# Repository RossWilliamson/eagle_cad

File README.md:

eagle_cad
=========

Eagle Projects

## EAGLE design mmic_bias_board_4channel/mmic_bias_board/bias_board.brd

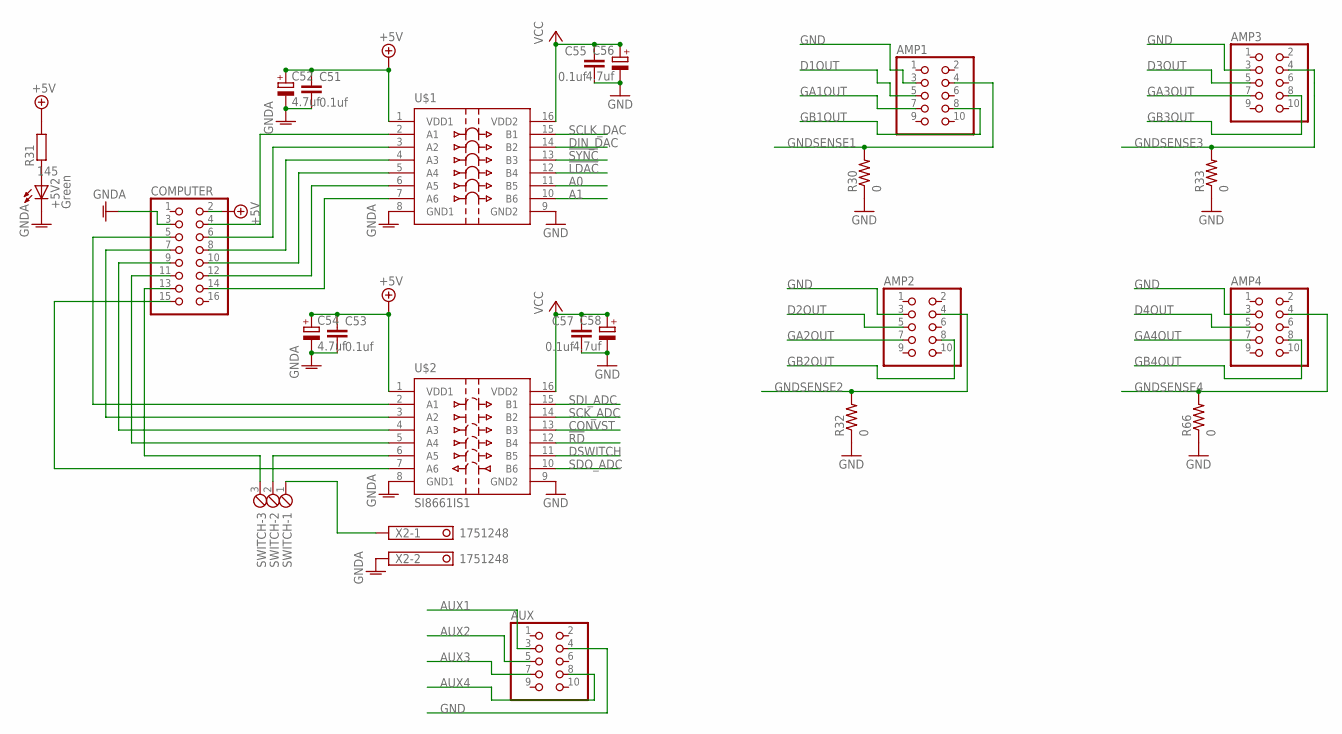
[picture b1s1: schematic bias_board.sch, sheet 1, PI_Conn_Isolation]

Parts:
+5V2: Green; 1206; MPN 01-901.5
AMP1, AMP2, AMP3, AMP4: PINHD-2X5; 2X05
AUX: PINHD-2X5; 2X05
C51, C53, C55, C57: 0.1uf; C1206; PARTNO C1206C104K3RACTU
C52, C54, C56, C58: 4.7uf; A/3216-18W; PARTNO T491A475M025AT
COMPUTER: PINHD-2X8; 2X08
R30, R32, R33, R66: 0; M1206
R31: 145; R1206; MPN MC0.125W12061%147R
SWITCH: MPT3; 3POL254
U$1: SI8660IS1; SO16
U$2: SI8661IS1; SO16
X2: 1751248

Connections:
!LDAC: U$1.12 (B4); also elsewhere on the board
!RD: U$2.12 (B4); also elsewhere on the board
!SYNC: U$1.13 (B3); also elsewhere on the board
+5V: C51.1, C52.+, C53.1, C54.+, COMPUTER.2, R31.2, U$1.1 (VDD1), U$2.1 (VDD1)
A0: U$1.11 (B5); also elsewhere on the board
A1: U$1.10 (B6); also elsewhere on the board
AUX1: AUX.3; also elsewhere on the board
AUX2: AUX.5; also elsewhere on the board
AUX3: AUX.7; also elsewhere on the board
AUX4: AUX.8; also elsewhere on the board
CONVST: U$2.13 (B3); also elsewhere on the board
D1OUT: AMP1.5; also elsewhere on the board
D2OUT: AMP2.5; also elsewhere on the board
D3OUT: AMP3.5; also elsewhere on the board
D4OUT: AMP4.5; also elsewhere on the board
DIN_DAC: U$1.14 (B2); also elsewhere on the board
DSWITCH: U$2.11 (B5); also elsewhere on the board
GA1OUT: AMP1.7; also elsewhere on the board
GA2OUT: AMP2.7; also elsewhere on the board
GA3OUT: AMP3.7; also elsewhere on the board
GA4OUT: AMP4.7; also elsewhere on the board
GB1OUT: AMP1.8; also elsewhere on the board
GB2OUT: AMP2.8; also elsewhere on the board
GB3OUT: AMP3.8; also elsewhere on the board
GB4OUT: AMP4.8; also elsewhere on the board
GND: AMP1.3, AMP2.3, AMP3.3, AMP4.3, AUX.4, C55.2, C56.-, C57.2, C58.-, R30.1, R32.1, R33.1, R66.1, U$1.9 (GND2), U$2.9 (GND2); also elsewhere on the board
GNDA: +5V2.C, C51.2, C52.-, C53.2, C54.-, COMPUTER.3, U$1.8 (GND1), U$2.8 (GND1), X2.2
GNDSENSE1: AMP1.4, R30.2; also elsewhere on the board
GNDSENSE2: AMP2.4, R32.2; also elsewhere on the board
GNDSENSE3: AMP3.4, R33.2; also elsewhere on the board
GNDSENSE4: AMP4.4, R66.2; also elsewhere on the board
unnamed: COMPUTER.10, U$1.5 (A4)
unnamed: COMPUTER.12, U$1.6 (A5)
unnamed: COMPUTER.11, U$2.5 (A4)
unnamed: COMPUTER.4, U$1.2 (A1)
unnamed: COMPUTER.6, U$1.3 (A2)
unnamed: COMPUTER.8, U$1.4 (A3)
unnamed: COMPUTER.5, U$2.2 (A1)
unnamed: COMPUTER.7, U$2.3 (A2)
unnamed: COMPUTER.9, U$2.4 (A3)
unnamed: COMPUTER.13, SWITCH.3
unnamed: COMPUTER.15, U$2.7 (A6)
unnamed: +5V2.A, R31.1
unnamed: SWITCH.2, U$2.6 (A5)
unnamed: SWITCH.1, X2.1
unnamed: COMPUTER.14, U$1.7 (A6)
SCK_ADC: U$2.14 (B2); also elsewhere on the board
SCLK_DAC: U$1.15 (B1); also elsewhere on the board
SDI_ADC: U$2.15 (B1); also elsewhere on the board
SDO_ADC: U$2.10 (B6); also elsewhere on the board
VCC: C55.1, C56.+, C57.1, C58.+, U$1.16 (VDD2), U$2.16 (VDD2); also elsewhere on the board

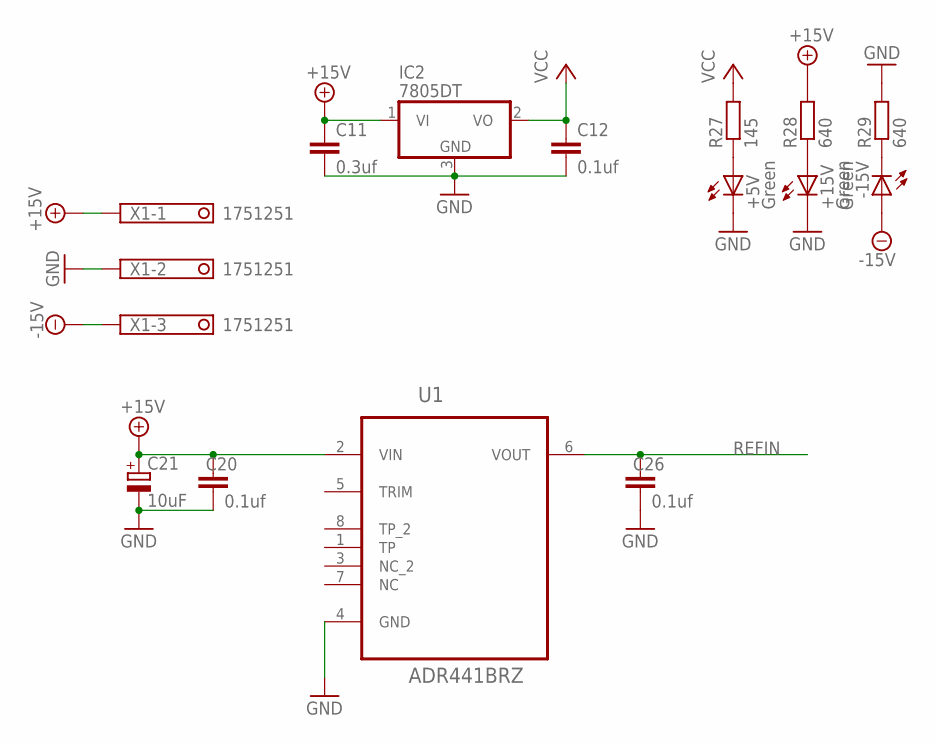
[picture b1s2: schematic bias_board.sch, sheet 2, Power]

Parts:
+5V, +15V: Green; 1206; MPN 01-901.5
-15V: Green; 1206; MPN 01-901.5
C11: 0.3uf; C1206; PARTNO C3216X7R1E334K
C12, C20, C26: 0.1uf; C1206; PARTNO C1206C104K3RACTU
C21: 10uF; A/3216-18W; PARTNO T491A475M025AT
IC2: 7805DT; TO252; PARTNO BA17805FP-E2
R27: 145; R1206; MPN MC0.125W12061%147R
R28, R29: 640; R1206; MPN MC0.125W12061%649R
U1: ADR441BRZ; SOIC127P600X175-8N
X1: 1751251

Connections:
+15V: C11.1, C20.1, C21.+, IC2.1 (VI), R28.2, U1.2 (VIN), X1.1; also elsewhere on the board
-15V: -15V.A, X1.3; also elsewhere on the board
GND: +5V.C, +15V.C, C11.2, C12.2, C20.2, C21.-, C26.2, IC2.3 (GND), R29.2, U1.4 (GND), X1.2; also elsewhere on the board
unnamed: +5V.A, R27.1
unnamed: +15V.A, R28.1
unnamed: -15V.C, R29.1
REFIN: C26.1, U1.6 (VOUT); also elsewhere on the board
VCC: C12.1, IC2.2 (VO), R27.2; also elsewhere on the board

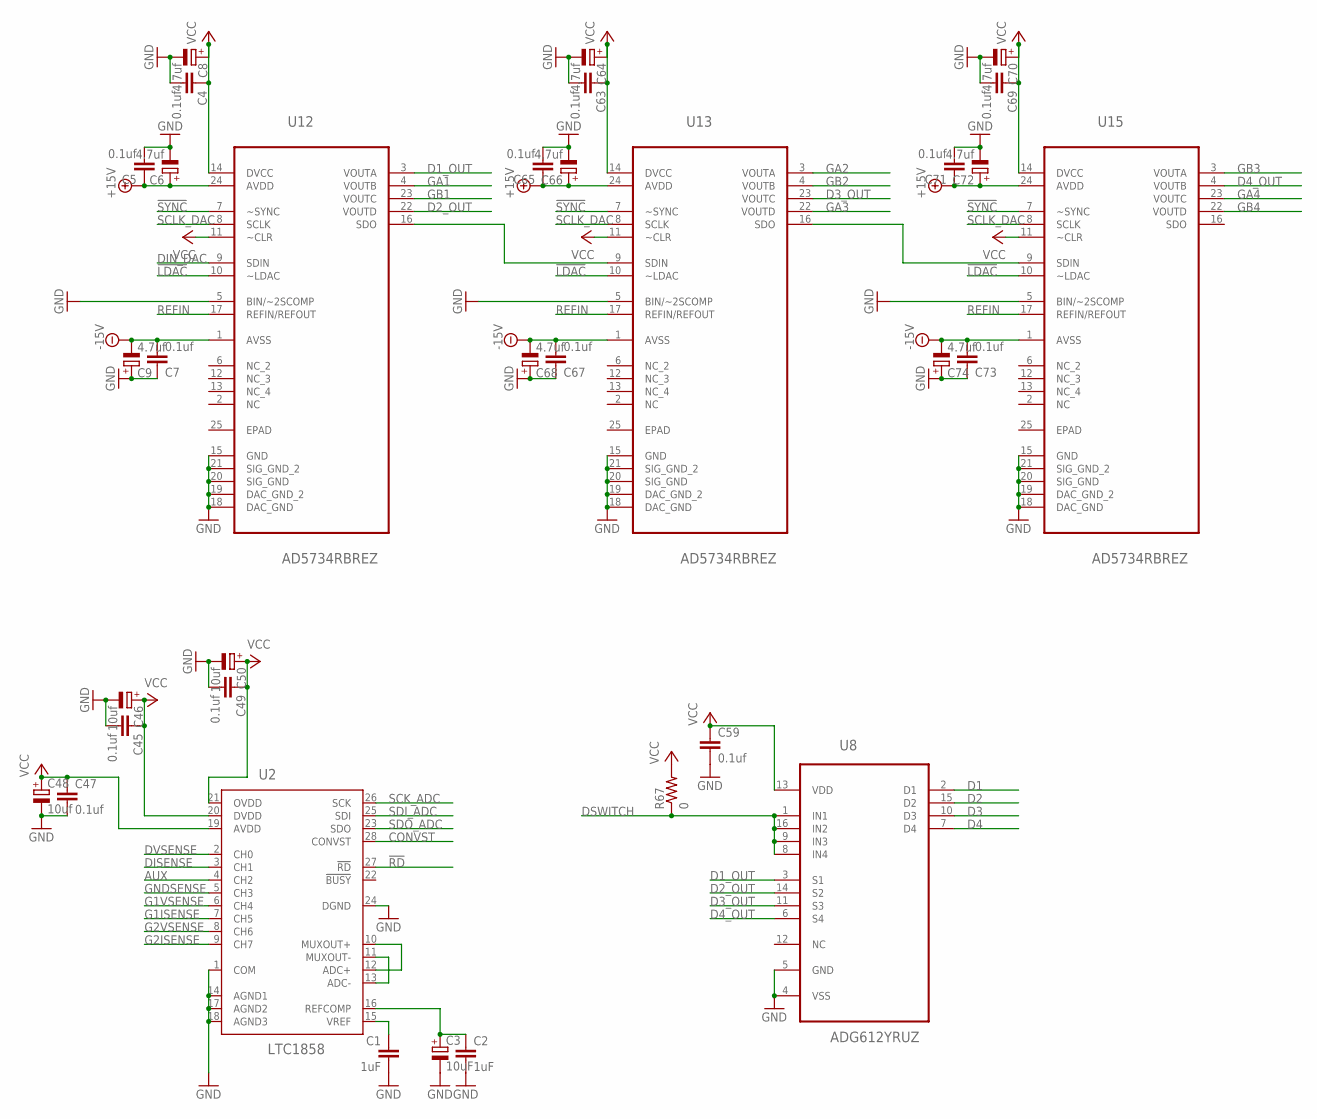
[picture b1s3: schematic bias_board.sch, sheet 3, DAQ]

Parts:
C1, C2: 1uF; C1206; PARTNO C1206C104K3RACTU
C3: 10uF; A/3216-18W; PARTNO T491A475M025AT
C4, C5, C7, C45, C47, C49, C59, C63, C65, C67, C69, C71, C73: 0.1uf; C1206; PARTNO C1206C104K3RACTU
C6, C8, C9, C64, C66, C68, C70, C72, C74: 4.7uf; A/3216-18W; PARTNO T491A475M025AT
C46, C48, C50: 10uf; A/3216-18W; PARTNO T491A475M025AT
R67: 0; M1206
U2: LTC1858; SSOP28
U8: ADG612YRUZ; SOP65P640X120-16N
U12, U13, U15: AD5734RBREZ; SOP65P640X120-25N

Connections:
!LDAC: U12.10 (~LDAC), U13.10 (~LDAC), U15.10 (~LDAC); also elsewhere on the board
!RD: U2.27 (!RD); also elsewhere on the board
!SYNC: U12.7 (~SYNC), U13.7 (~SYNC), U15.7 (~SYNC); also elsewhere on the board
+15V: C5.1, C6.+, C65.1, C66.+, C71.1, C72.+, U12.24 (AVDD), U13.24 (AVDD), U15.24 (AVDD); also elsewhere on the board
-15V: C7.2, C9.-, C67.2, C68.-, C73.2, C74.-, U12.1 (AVSS), U13.1 (AVSS), U15.1 (AVSS); also elsewhere on the board
AUX: U2.4 (CH2); also elsewhere on the board
CONVST: U2.28 (CONVST); also elsewhere on the board
D1: U8.2 (D1); also elsewhere on the board
D1_OUT: U8.3 (S1), U12.3 (VOUTA)
D2: U8.15 (D2); also elsewhere on the board
D2_OUT: U8.14 (S2), U12.22 (VOUTD)
D3: U8.10 (D3); also elsewhere on the board
D3_OUT: U8.11 (S3), U13.23 (VOUTC)
D4: U8.7 (D4); also elsewhere on the board
D4_OUT: U8.6 (S4), U15.4 (VOUTB)
DIN_DAC: U12.9 (SDIN); also elsewhere on the board
DISENSE: U2.3 (CH1); also elsewhere on the board
DSWITCH: R67.1, U8.1 (IN1), U8.8 (IN4), U8.9 (IN3), U8.16 (IN2); also elsewhere on the board
DVSENSE: U2.2 (CH0); also elsewhere on the board
EPAD: U12.25 (EPAD), U13.25 (EPAD), U15.25 (EPAD)
G1ISENSE: U2.7 (CH5); also elsewhere on the board
G1VSENSE: U2.6 (CH4); also elsewhere on the board
G2ISENSE: U2.9 (CH7); also elsewhere on the board
G2VSENSE: U2.8 (CH6); also elsewhere on the board
GA1: U12.4 (VOUTB); also elsewhere on the board
GA2: U13.3 (VOUTA); also elsewhere on the board
GA3: U13.22 (VOUTD); also elsewhere on the board
GA4: U15.23 (VOUTC); also elsewhere on the board
GB1: U12.23 (VOUTC); also elsewhere on the board
GB2: U13.4 (VOUTB); also elsewhere on the board
GB3: U15.3 (VOUTA); also elsewhere on the board
GB4: U15.22 (VOUTD); also elsewhere on the board
GND: C1.2, C2.2, C3.-, C4.2, C5.2, C6.-, C7.1, C8.-, C9.+, C45.2, C46.-, C47.2, C48.-, C49.2, C50.-, C59.2, C63.2, C64.-, C65.2, C66.-, C67.1, C68.+, C69.2, C70.-, C71.2, C72.-, C73.1, C74.+, U2.1 (COM), U2.14 (AGND1), U2.17 (AGND2), U2.18 (AGND3), U2.24 (DGND), U8.4 (VSS), U8.5 (GND), U12.5 (BIN/~2SCOMP), U12.15 (GND), U12.18 (DAC_GND), U12.19 (DAC_GND_2), U12.20 (SIG_GND), U12.21 (SIG_GND_2), U13.5 (BIN/~2SCOMP), U13.15 (GND), U13.18 (DAC_GND), U13.19 (DAC_GND_2), U13.20 (SIG_GND), U13.21 (SIG_GND_2), U15.5 (BIN/~2SCOMP), U15.15 (GND), U15.18 (DAC_GND), U15.19 (DAC_GND_2), U15.20 (SIG_GND), U15.21 (SIG_GND_2); also elsewhere on the board
GNDSENSE: U2.5 (CH3); also elsewhere on the board
unnamed: C1.1, U2.15 (VREF)
unnamed: C2.1, C3.+, U2.16 (REFCOMP)
unnamed: U2.10 (MUXOUT+), U2.12 (ADC+)
unnamed: U2.11 (MUXOUT-), U2.13 (ADC-)
unnamed: U12.16 (SDO), U13.9 (SDIN)
unnamed: U13.16 (SDO), U15.9 (SDIN)
REFIN: U12.17 (REFIN/REFOUT), U13.17 (REFIN/REFOUT), U15.17 (REFIN/REFOUT); also elsewhere on the board
SCK_ADC: U2.26 (SCK); also elsewhere on the board
SCLK_DAC: U12.8 (SCLK), U13.8 (SCLK), U15.8 (SCLK); also elsewhere on the board
SDI_ADC: U2.25 (SDI); also elsewhere on the board
SDO_ADC: U2.23 (SDO); also elsewhere on the board
VCC: C4.1, C8.+, C45.1, C46.+, C47.1, C48.+, C49.1, C50.+, C59.1, C63.1, C64.+, C69.1, C70.+, R67.2, U2.19 (AVDD), U2.20 (DVDD), U2.21 (OVDD), U8.13 (VDD), U12.11 (~CLR), U12.14 (DVCC), U13.11 (~CLR), U13.14 (DVCC), U15.11 (~CLR), U15.14 (DVCC); also elsewhere on the board

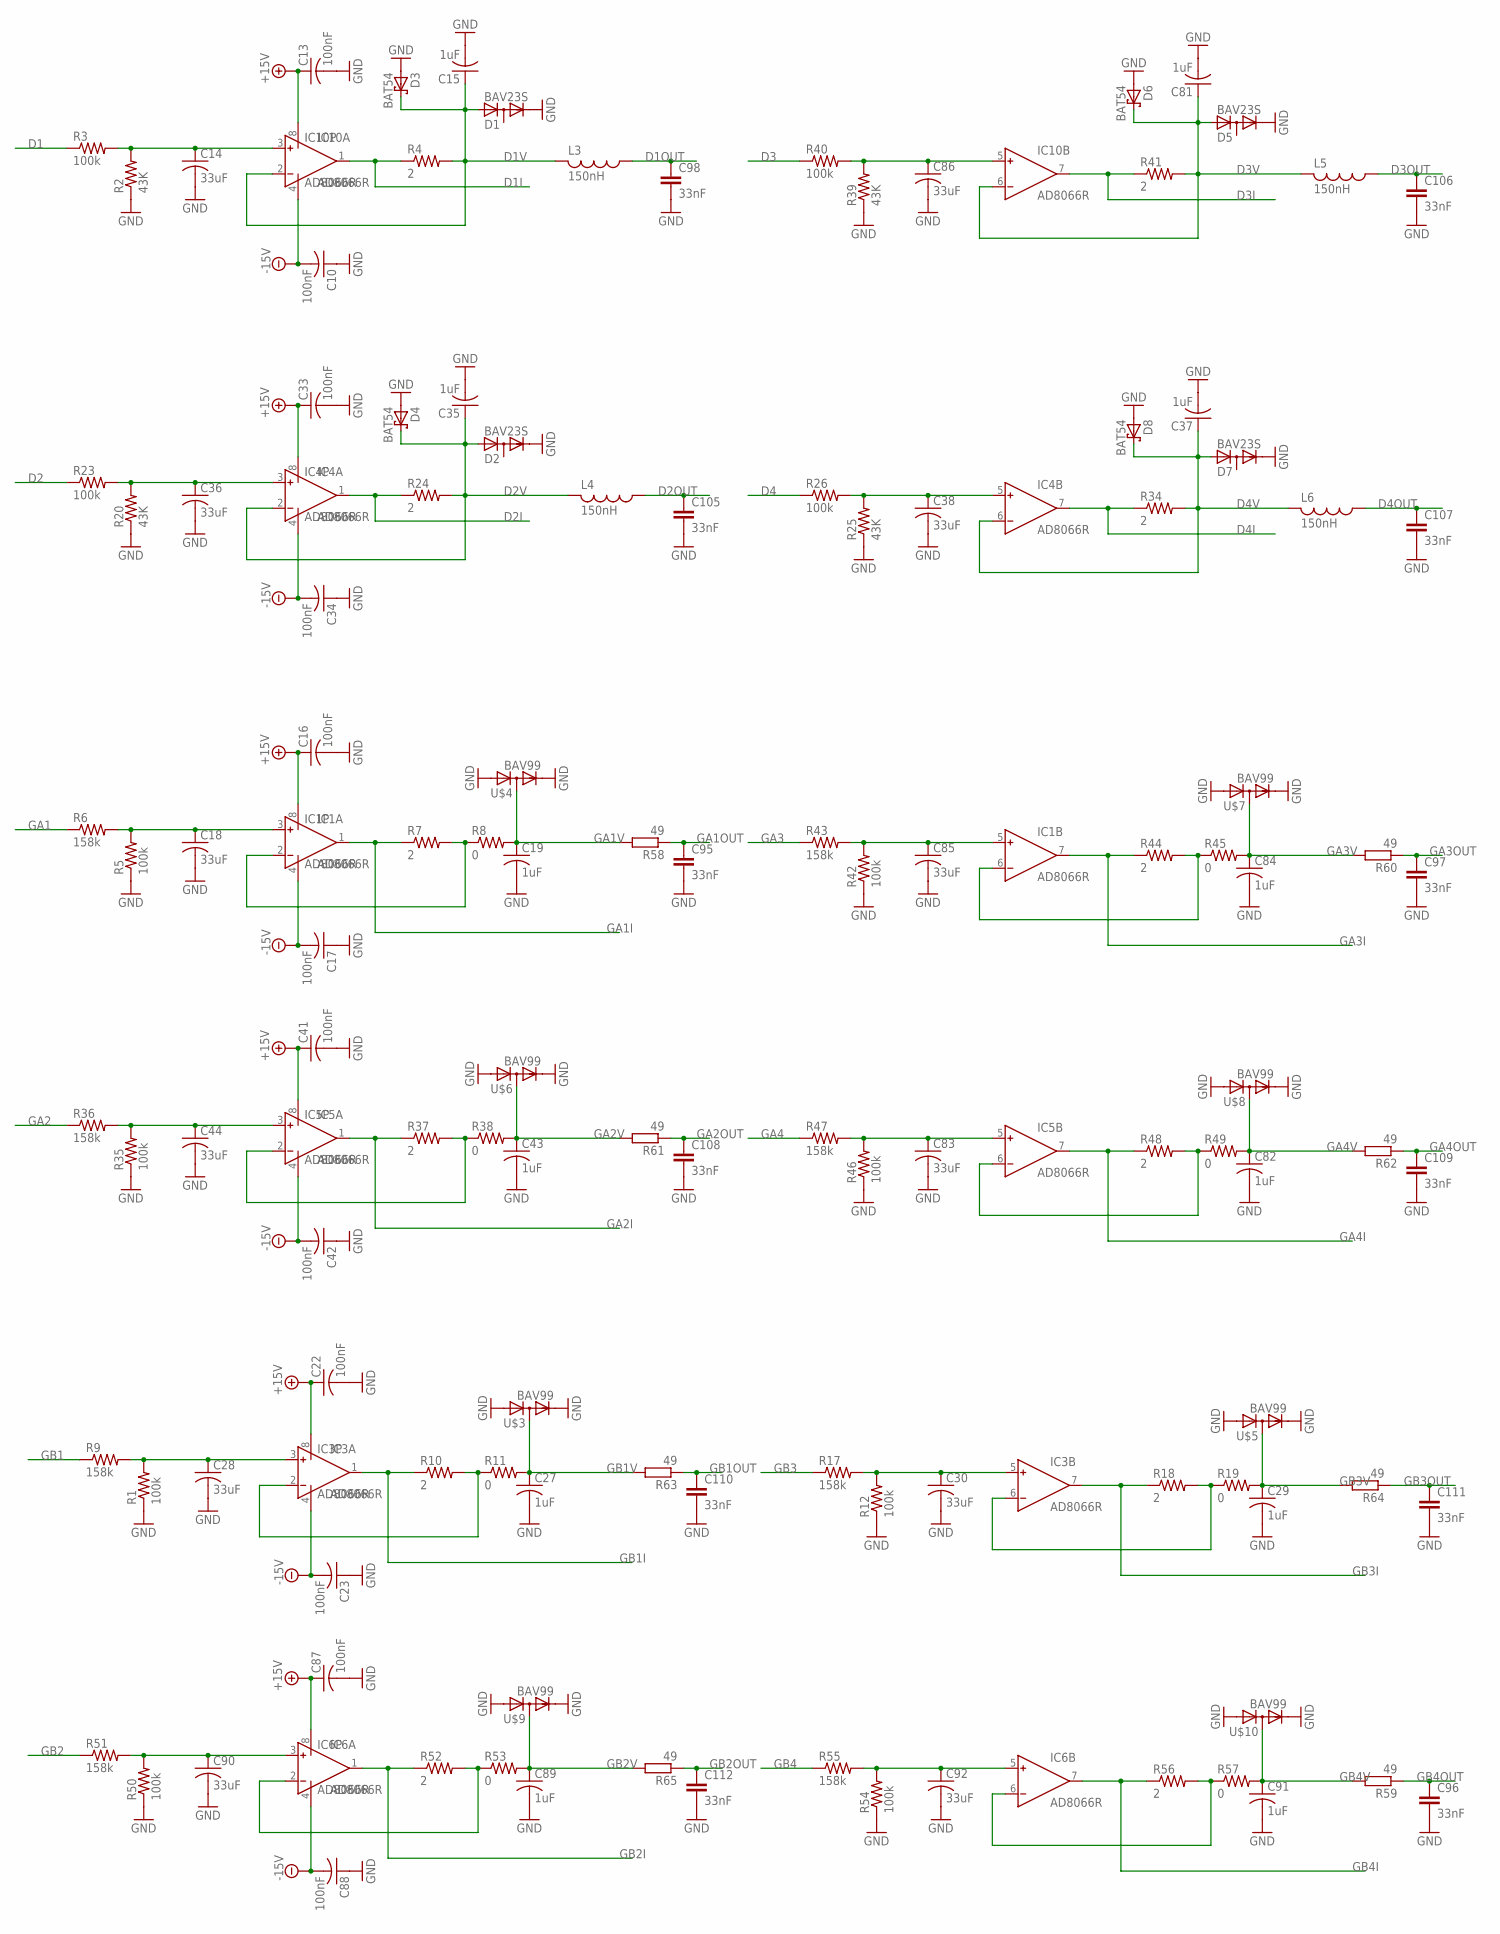
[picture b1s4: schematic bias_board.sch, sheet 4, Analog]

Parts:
C10, C13, C16, C17, C22, C23, C33, C34, C41, C42, C87, C88: 100nF; C1206K
C14, C18, C28, C30, C36, C38, C44, C83, C85, C86, C90, C92: 33uF; C1206K
C15, C19, C27, C29, C35, C37, C43, C81, C82, C84, C89, C91: 1uF; C1206K
C95, C96, C97, C98, C105, C106, C107, C108, C109, C110, C111, C112: 33nF; C1206; PARTNO C1206C104K3RACTU
D1, D2, D5, D7: BAV23S; SOT23
D3, D4, D6, D8: BAT54; SOT23
IC1, IC3, IC4, IC5, IC6, IC10: AD8066R; SO8
L3, L4, L5, L6: 150nH; L3225M
R1, R3, R5, R12, R23, R26, R35, R40, R42, R46, R50, R54: 100k; M1206
R2, R20, R25, R39: 43K; M1206
R4, R7, R10, R18, R24, R34, R37, R41, R44, R48, R52, R56: 2; M1206
R6, R9, R17, R36, R43, R47, R51, R55: 158k; M1206
R8, R11, R19, R38, R45, R49, R53, R57: 0; M1206
R58, R59, R60, R61, R62, R63, R64, R65: 49; R1206; MPN MC0.125W12061%147R
U$3, U$4, U$5, U$6, U$7, U$8, U$9, U$10: BAV99; SOT23

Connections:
+15V: C13.1, C16.1, C22.1, C33.1, C41.1, C87.1, IC1.8 (V+), IC3.8 (V+), IC4.8 (V+), IC5.8 (V+), IC6.8 (V+), IC10.8 (V+); also elsewhere on the board
-15V: C10.2, C17.2, C23.2, C34.2, C42.2, C88.2, IC1.4 (V-), IC3.4 (V-), IC4.4 (V-), IC5.4 (V-), IC6.4 (V-), IC10.4 (V-); also elsewhere on the board
D1: R3.1; also elsewhere on the board
D1I: IC10.1 (OUT), R4.1; also elsewhere on the board
D1OUT: C98.1, L3.1; also elsewhere on the board
D1V: C15.1, D1.1 (A), D3.3 (C), IC10.2 (IN-), L3.2, R4.2; also elsewhere on the board
D2: R23.1; also elsewhere on the board
D2I: IC4.1 (OUT), R24.1; also elsewhere on the board
D2OUT: C105.1, L4.1; also elsewhere on the board
D2V: C35.1, D2.1 (A), D4.3 (C), IC4.2 (IN-), L4.2, R24.2; also elsewhere on the board
D3: R40.1; also elsewhere on the board
D3I: IC10.7 (OUT), R41.1; also elsewhere on the board
D3OUT: C106.1, L5.1; also elsewhere on the board
D3V: C81.1, D5.1 (A), D6.3 (C), IC10.6 (IN-), L5.2, R41.2; also elsewhere on the board
D4: R26.1; also elsewhere on the board
D4I: IC4.7 (OUT), R34.1; also elsewhere on the board
D4OUT: C107.1, L6.1; also elsewhere on the board
D4V: C37.1, D7.1 (A), D8.3 (C), IC4.6 (IN-), L6.2, R34.2; also elsewhere on the board
GA1: R6.1; also elsewhere on the board
GA1I: IC1.1 (OUT), R7.1; also elsewhere on the board
GA1OUT: C95.1, R58.1; also elsewhere on the board
GA1V: C19.1, R8.2, R58.2, U$4.3 (AC); also elsewhere on the board
GA2: R36.1; also elsewhere on the board
GA2I: IC5.1 (OUT), R37.1; also elsewhere on the board
GA2OUT: C108.1, R61.1; also elsewhere on the board
GA2V: C43.1, R38.2, R61.2, U$6.3 (AC); also elsewhere on the board
GA3: R43.1; also elsewhere on the board
GA3I: IC1.7 (OUT), R44.1; also elsewhere on the board
GA3OUT: C97.1, R60.1; also elsewhere on the board
GA3V: C84.1, R45.2, R60.2, U$7.3 (AC); also elsewhere on the board
GA4: R47.1; also elsewhere on the board
GA4I: IC5.7 (OUT), R48.1; also elsewhere on the board
GA4OUT: C109.1, R62.1; also elsewhere on the board
GA4V: C82.1, R49.2, R62.2, U$8.3 (AC); also elsewhere on the board
GB1: R9.1; also elsewhere on the board
GB1I: IC3.1 (OUT), R10.1; also elsewhere on the board
GB1OUT: C110.1, R63.1; also elsewhere on the board
GB1V: C27.1, R11.2, R63.2, U$3.3 (AC); also elsewhere on the board
GB2: R51.1; also elsewhere on the board
GB2I: IC6.1 (OUT), R52.1; also elsewhere on the board
GB2OUT: C112.1, R65.1; also elsewhere on the board
GB2V: C89.1, R53.2, R65.2, U$9.3 (AC); also elsewhere on the board
GB3: R17.1; also elsewhere on the board
GB3I: IC3.7 (OUT), R18.1; also elsewhere on the board
GB3OUT: C111.1, R64.1; also elsewhere on the board
GB3V: C29.1, R19.2, R64.2, U$5.3 (AC); also elsewhere on the board
GB4: R55.1; also elsewhere on the board
GB4I: IC6.7 (OUT), R56.1; also elsewhere on the board
GB4OUT: C96.1, R59.1; also elsewhere on the board
GB4V: C91.1, R57.2, R59.2, U$10.3 (AC); also elsewhere on the board
GND: C10.1, C13.2, C14.2, C15.2, C16.2, C17.1, C18.2, C19.2, C22.2, C23.1, C27.2, C28.2, C29.2, C30.2, C33.2, C34.1, C35.2, C36.2, C37.2, C38.2, C41.2, C42.1, C43.2, C44.2, C81.2, C82.2, C83.2, C84.2, C85.2, C86.2, C87.2, C88.1, C89.2, C90.2, C91.2, C92.2, C95.2, C96.2, C97.2, C98.2, C105.2, C106.2, C107.2, C108.2, C109.2, C110.2, C111.2, C112.2, D1.2 (C), D2.2 (C), D3.1 (A), D4.1 (A), D5.2 (C), D6.1 (A), D7.2 (C), D8.1 (A), R1.1, R2.1, R5.1, R12.1, R20.1, R25.1, R35.1, R39.1, R42.1, R46.1, R50.1, R54.1, U$3.1 (A), U$3.2 (C), U$4.1 (A), U$4.2 (C), U$5.1 (A), U$5.2 (C), U$6.1 (A), U$6.2 (C), U$7.1 (A), U$7.2 (C), U$8.1 (A), U$8.2 (C), U$9.1 (A), U$9.2 (C), U$10.1 (A), U$10.2 (C); also elsewhere on the board
unnamed: C14.1, IC10.3 (IN+), R2.2, R3.2
unnamed: C28.1, IC3.3 (IN+), R1.2, R9.2
unnamed: C18.1, IC1.3 (IN+), R5.2, R6.2
unnamed: IC3.2 (IN-), R10.2, R11.1
unnamed: C30.1, IC3.5 (IN+), R12.2, R17.2
unnamed: IC1.2 (IN-), R7.2, R8.1
unnamed: IC3.6 (IN-), R18.2, R19.1
unnamed: C36.1, IC4.3 (IN+), R20.2, R23.2
unnamed: C38.1, IC4.5 (IN+), R25.2, R26.2
unnamed: C44.1, IC5.3 (IN+), R35.2, R36.2
unnamed: C86.1, IC10.5 (IN+), R39.2, R40.2
unnamed: C85.1, IC1.5 (IN+), R42.2, R43.2
unnamed: IC1.6 (IN-), R44.2, R45.1
unnamed: IC5.2 (IN-), R37.2, R38.1
unnamed: C83.1, IC5.5 (IN+), R46.2, R47.2
unnamed: IC5.6 (IN-), R48.2, R49.1
unnamed: C90.1, IC6.3 (IN+), R50.2, R51.2
unnamed: IC6.2 (IN-), R52.2, R53.1
unnamed: C92.1, IC6.5 (IN+), R54.2, R55.2
unnamed: IC6.6 (IN-), R56.2, R57.1

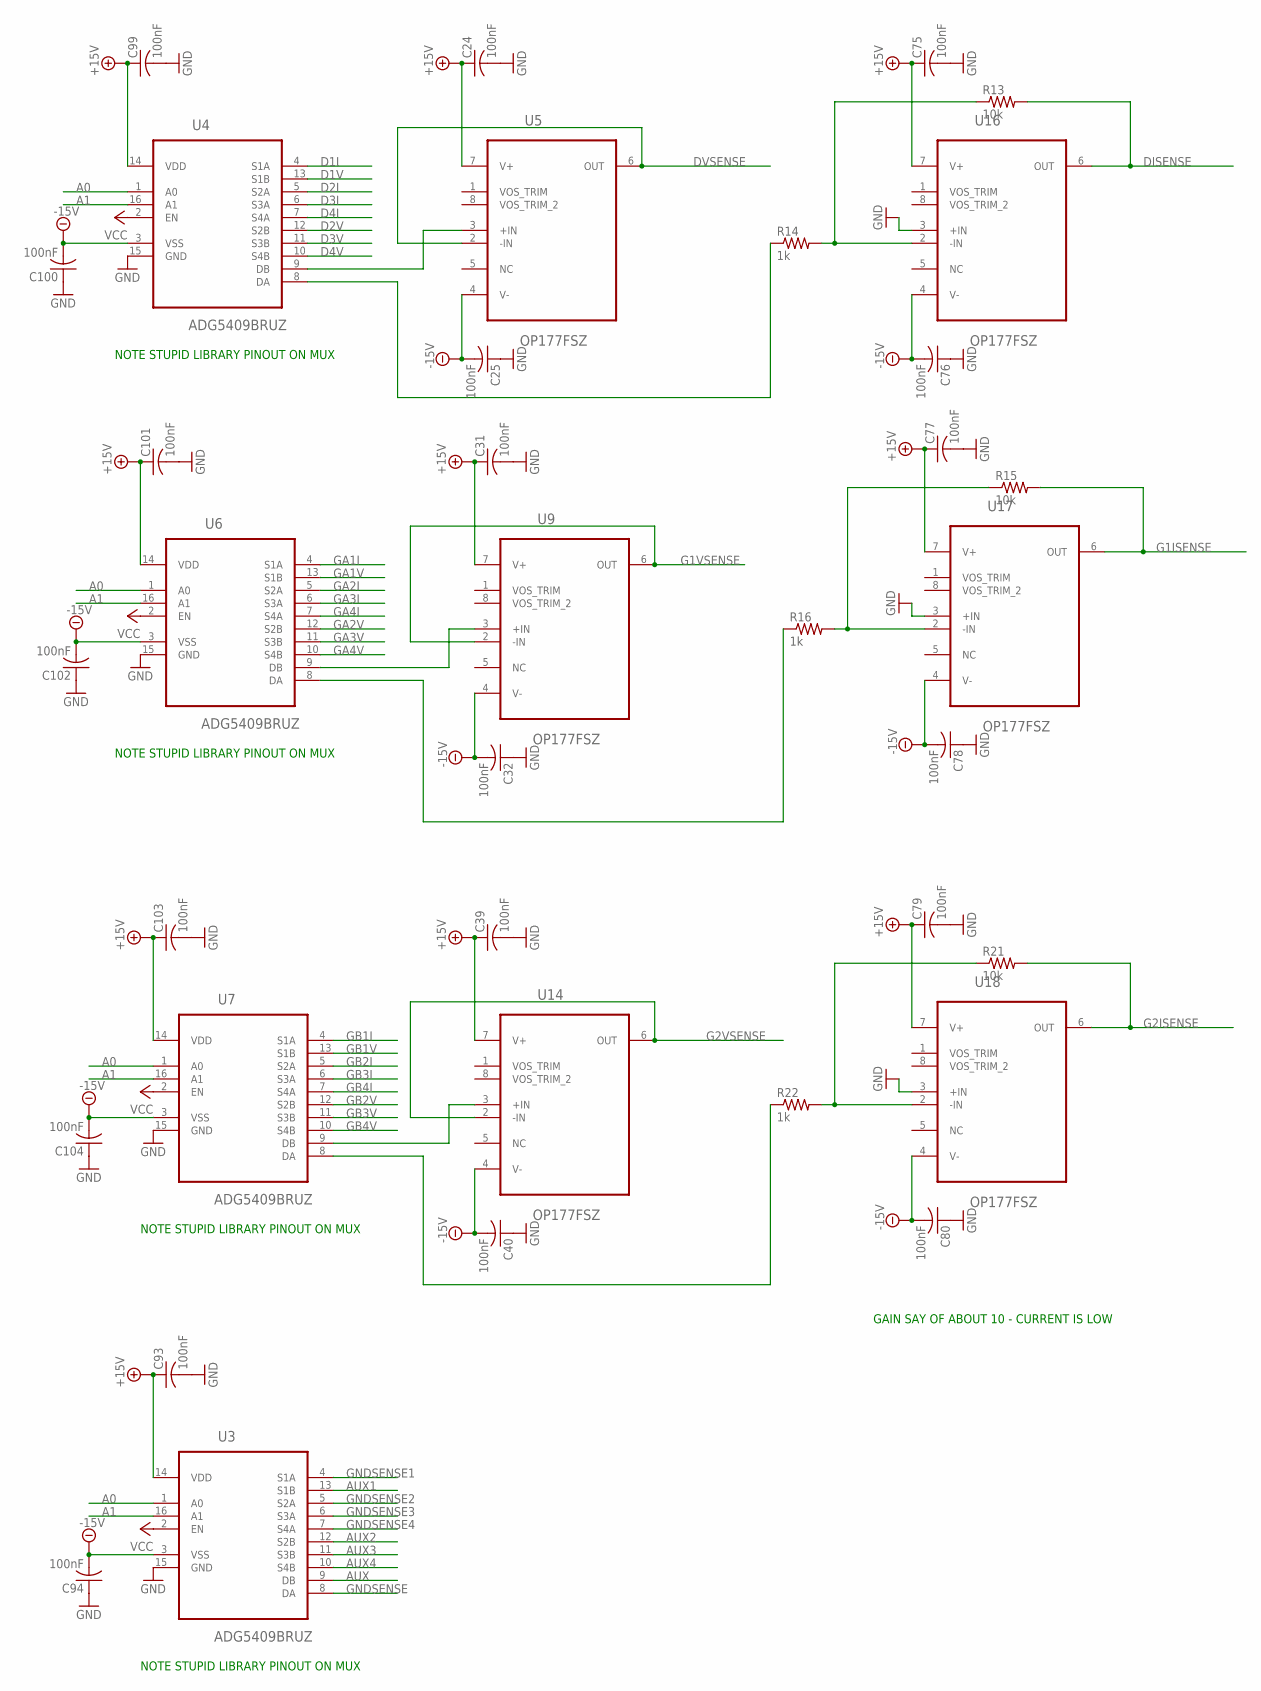
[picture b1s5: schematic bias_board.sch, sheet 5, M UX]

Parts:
C24, C25, C31, C32, C39, C40, C75, C76, C77, C78, C79, C80, C93, C94, C99, C100, C101, C102, C103, C104: 100nF; C1206K
R13, R15, R21: 10k; M1206
R14, R16, R22: 1k; M1206
U3, U4, U6, U7: ADG5409BRUZ; SOP65P640X120-16N
U5, U9, U14, U16, U17, U18: OP177FSZ; SOIC127P600X175-8N

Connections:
+15V: C24.1, C31.1, C39.1, C75.1, C77.1, C79.1, C93.1, C99.1, C101.1, C103.1, U3.14 (VDD), U4.14 (VDD), U5.7 (V+), U6.14 (VDD), U7.14 (VDD), U9.7 (V+), U14.7 (V+), U16.7 (V+), U17.7 (V+), U18.7 (V+); also elsewhere on the board
-15V: C25.2, C32.2, C40.2, C76.2, C78.2, C80.2, C94.2, C100.2, C102.2, C104.2, U3.3 (VSS), U4.3 (VSS), U5.4 (V-), U6.3 (VSS), U7.3 (VSS), U9.4 (V-), U14.4 (V-), U16.4 (V-), U17.4 (V-), U18.4 (V-); also elsewhere on the board
A0: U3.1 (A0), U4.1 (A0), U6.1 (A0), U7.1 (A0); also elsewhere on the board
A1: U3.16 (A1), U4.16 (A1), U6.16 (A1), U7.16 (A1); also elsewhere on the board
AUX: U3.9 (DB); also elsewhere on the board
AUX1: U3.13 (S1B); also elsewhere on the board
AUX2: U3.12 (S2B); also elsewhere on the board
AUX3: U3.11 (S3B); also elsewhere on the board
AUX4: U3.10 (S4B); also elsewhere on the board
D1I: U4.4 (S1A); also elsewhere on the board
D1V: U4.13 (S1B); also elsewhere on the board
D2I: U4.5 (S2A); also elsewhere on the board
D2V: U4.12 (S2B); also elsewhere on the board
D3I: U4.6 (S3A); also elsewhere on the board
D3V: U4.11 (S3B); also elsewhere on the board
D4I: U4.7 (S4A); also elsewhere on the board
D4V: U4.10 (S4B); also elsewhere on the board
DISENSE: R13.2, U16.6 (OUT); also elsewhere on the board
DVSENSE: U5.2 (-IN), U5.6 (OUT); also elsewhere on the board
G1ISENSE: R15.2, U17.6 (OUT); also elsewhere on the board
G1V1: U6.9 (DB), U9.3 (+IN)
G1VSENSE: U9.2 (-IN), U9.6 (OUT); also elsewhere on the board
G2ISENSE: R21.2, U18.6 (OUT); also elsewhere on the board
G2VSENSE: U14.2 (-IN), U14.6 (OUT); also elsewhere on the board
GA1I: U6.4 (S1A); also elsewhere on the board
GA1V: U6.13 (S1B); also elsewhere on the board
GA2I: U6.5 (S2A); also elsewhere on the board
GA2V: U6.12 (S2B); also elsewhere on the board
GA3I: U6.6 (S3A); also elsewhere on the board
GA3V: U6.11 (S3B); also elsewhere on the board
GA4I: U6.7 (S4A); also elsewhere on the board
GA4V: U6.10 (S4B); also elsewhere on the board
GB1I: U7.4 (S1A); also elsewhere on the board
GB1V: U7.13 (S1B); also elsewhere on the board
GB2I: U7.5 (S2A); also elsewhere on the board
GB2V: U7.12 (S2B); also elsewhere on the board
GB3I: U7.6 (S3A); also elsewhere on the board
GB3V: U7.11 (S3B); also elsewhere on the board
GB4I: U7.7 (S4A); also elsewhere on the board
GB4V: U7.10 (S4B); also elsewhere on the board
GND: C24.2, C25.1, C31.2, C32.1, C39.2, C40.1, C75.2, C76.1, C77.2, C78.1, C79.2, C80.1, C93.2, C94.1, C99.2, C100.1, C101.2, C102.1, C103.2, C104.1, U3.15 (GND), U4.15 (GND), U6.15 (GND), U7.15 (GND), U16.3 (+IN), U17.3 (+IN), U18.3 (+IN); also elsewhere on the board
GNDSENSE: U3.8 (DA); also elsewhere on the board
GNDSENSE1: U3.4 (S1A); also elsewhere on the board
GNDSENSE2: U3.5 (S2A); also elsewhere on the board
GNDSENSE3: U3.6 (S3A); also elsewhere on the board
GNDSENSE4: U3.7 (S4A); also elsewhere on the board
unnamed: R13.1, R14.2, U16.2 (-IN)
unnamed: R15.1, R16.2, U17.2 (-IN)
unnamed: R21.1, R22.2, U18.2 (-IN)
unnamed: U4.9 (DB), U5.3 (+IN)
unnamed: R14.1, U4.8 (DA)
unnamed: R16.1, U6.8 (DA)
unnamed: U7.9 (DB), U14.3 (+IN)
unnamed: R22.1, U7.8 (DA)
VCC: U3.2 (EN), U4.2 (EN), U6.2 (EN), U7.2 (EN); also elsewhere on the board

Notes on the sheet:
GAIN SAY OF ABOUT 10 - CURRENT IS LOW
NOTE STUPID LIBRARY PINOUT ON MUX

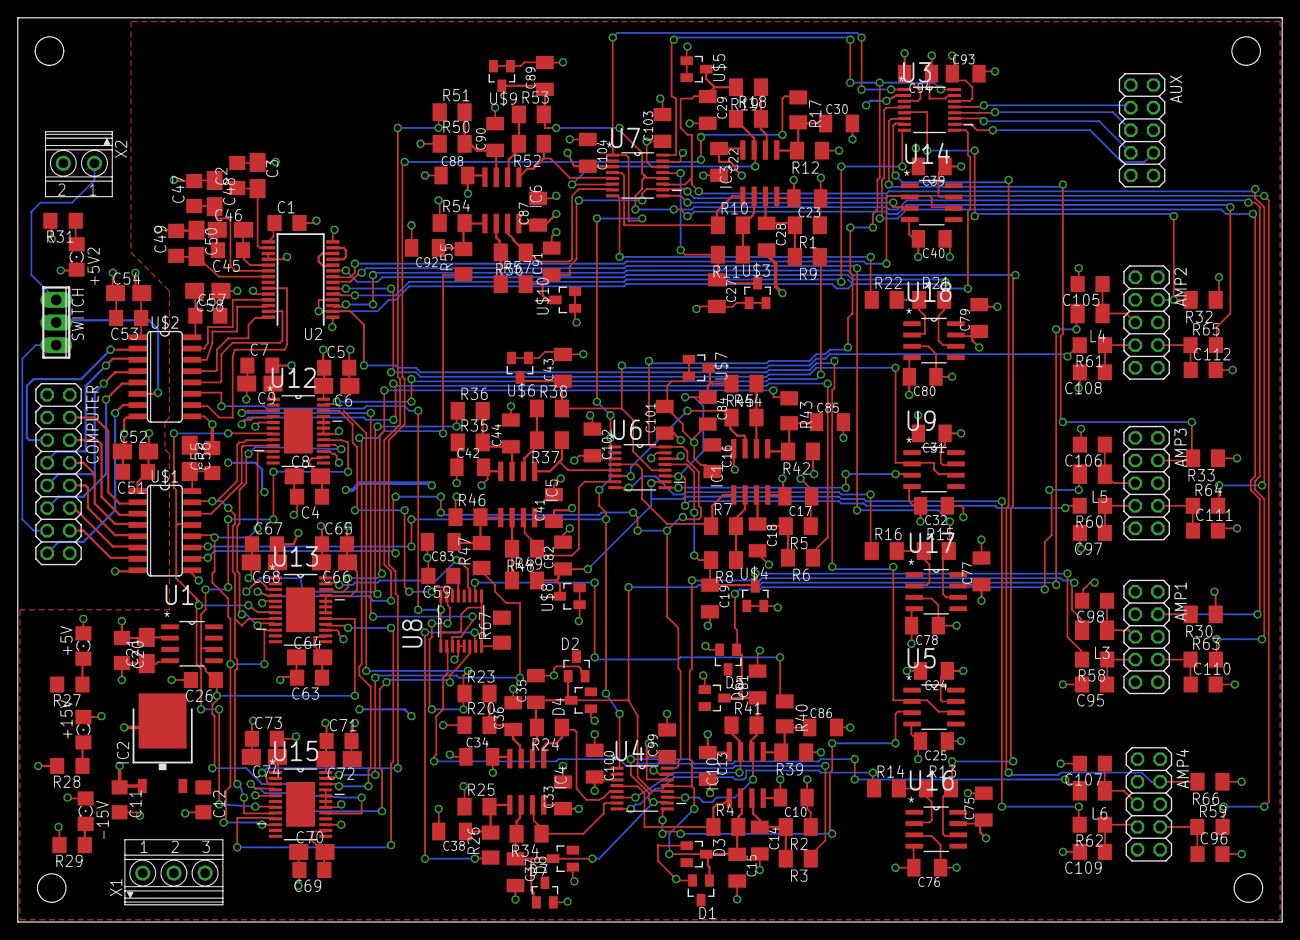
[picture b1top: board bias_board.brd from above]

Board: 4 copper layers, 142.0 x 101.5 mm, 234 parts (0 on the bottom side), 141 nets.

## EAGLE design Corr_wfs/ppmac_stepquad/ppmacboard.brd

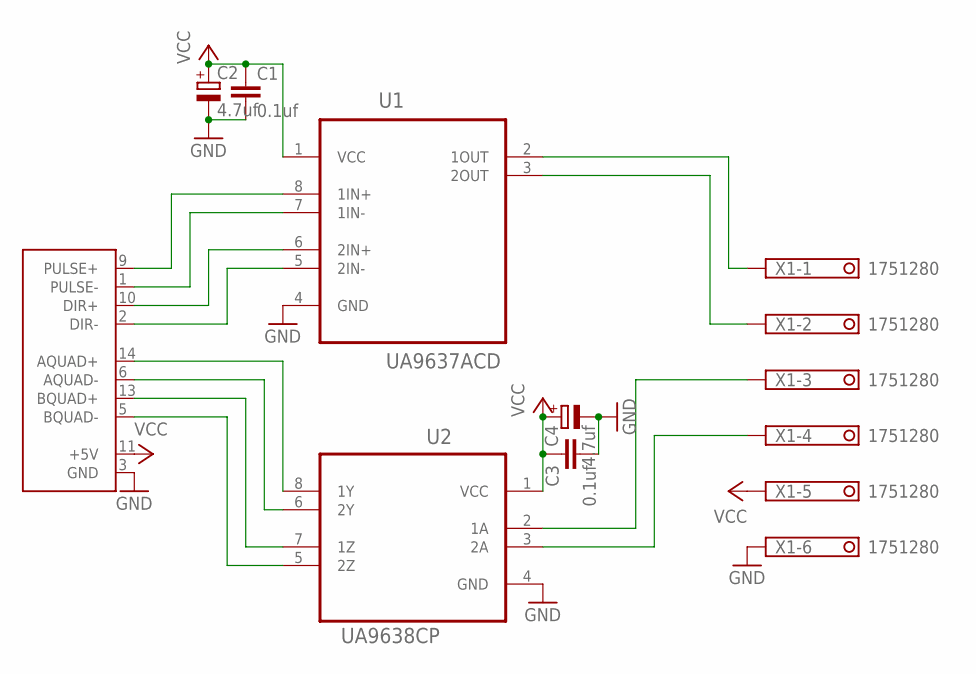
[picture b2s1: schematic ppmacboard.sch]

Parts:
C1, C3: 0.1uf; C1206; PARTNO C1206C104K3RACTU
C2, C4: 4.7uf; A/3216-18W; PARTNO T491A475M025AT
U1: UA9637ACD; SOIC127P600X175-8N
U2: UA9638CP; SOIC127P600X272-8N
U$1: AFBPUQUOUT; M15HP
X1: 1751280

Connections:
GND: C1.2, C2.-, C3.2, C4.-, U1.4 (GND), U2.4 (GND), U$1.3 (GND), X1.6
unnamed: U1.8 (1IN+), U$1.9 (PULSE+)
unnamed: U1.7 (1IN-), U$1.1 (PULSE-)
unnamed: U1.6 (2IN+), U$1.10 (DIR+)
unnamed: U1.5 (2IN-), U$1.2 (DIR-)
unnamed: U2.8 (1Y), U$1.14 (AQUAD+)
unnamed: U2.6 (2Y), U$1.6 (AQUAD-)
unnamed: U2.7 (1Z), U$1.13 (BQUAD+)
unnamed: U2.5 (2Z), U$1.5 (BQUAD-)
unnamed: U1.2 (1OUT), X1.1
unnamed: U1.3 (2OUT), X1.2
unnamed: U2.2 (1A), X1.3
unnamed: U2.3 (2A), X1.4
VCC: C1.1, C2.+, C3.1, C4.+, U1.1 (VCC), U2.1 (VCC), U$1.11 (+5V), X1.5

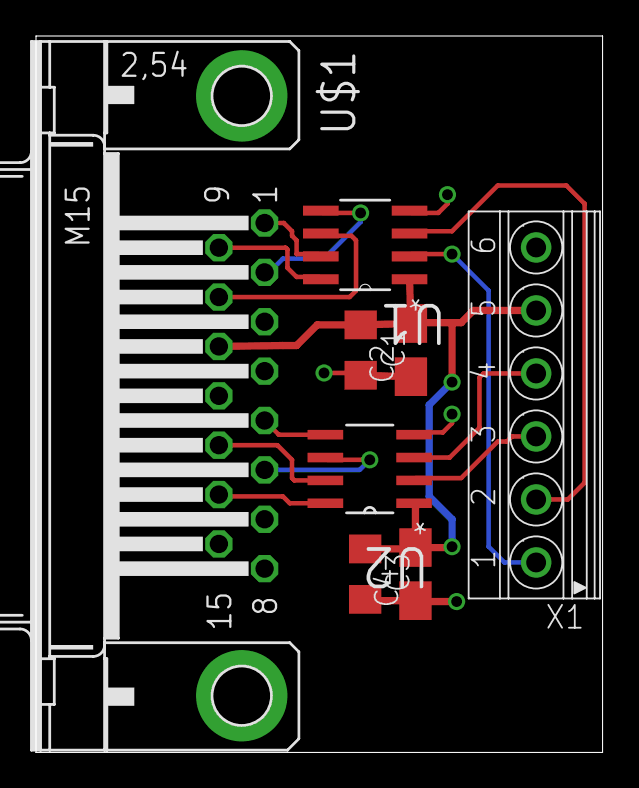
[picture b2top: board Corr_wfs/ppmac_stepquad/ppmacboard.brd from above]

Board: 2 copper layers, 31.5 x 39.8 mm, 8 parts (0 on the bottom side), 14 nets.
